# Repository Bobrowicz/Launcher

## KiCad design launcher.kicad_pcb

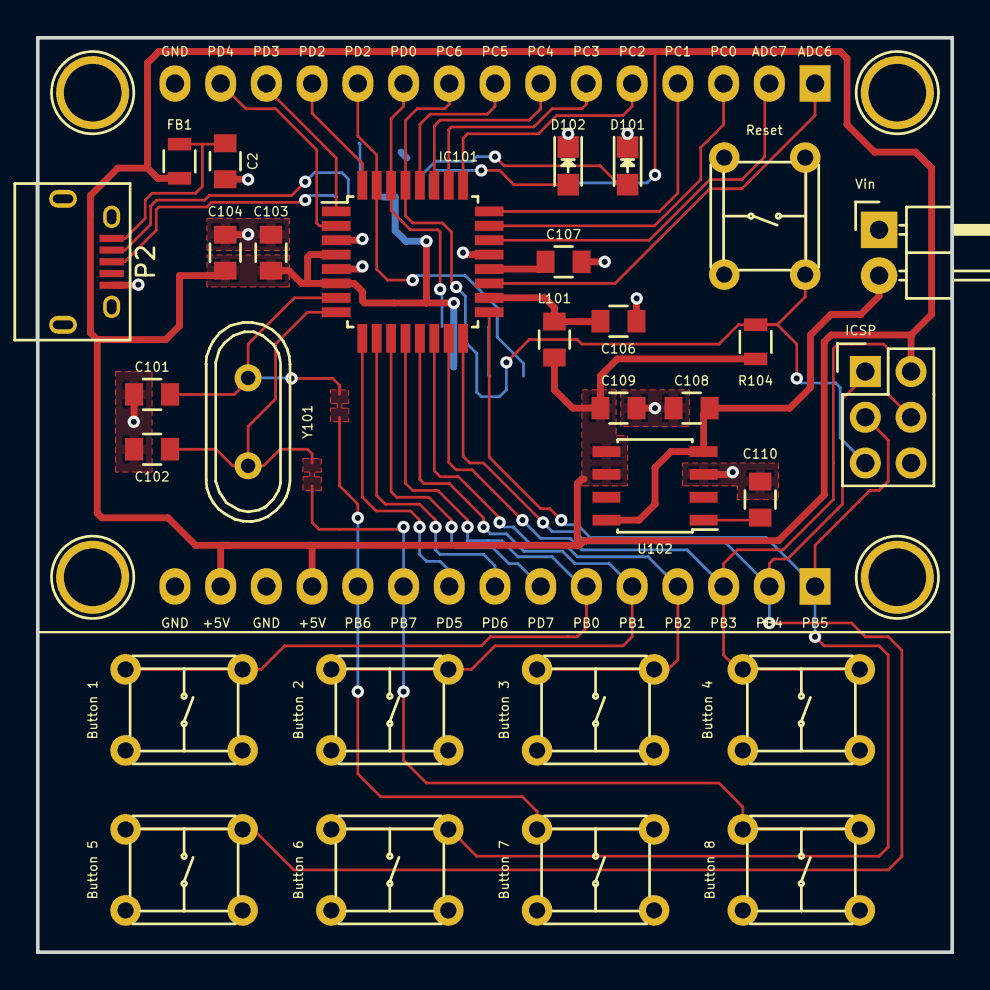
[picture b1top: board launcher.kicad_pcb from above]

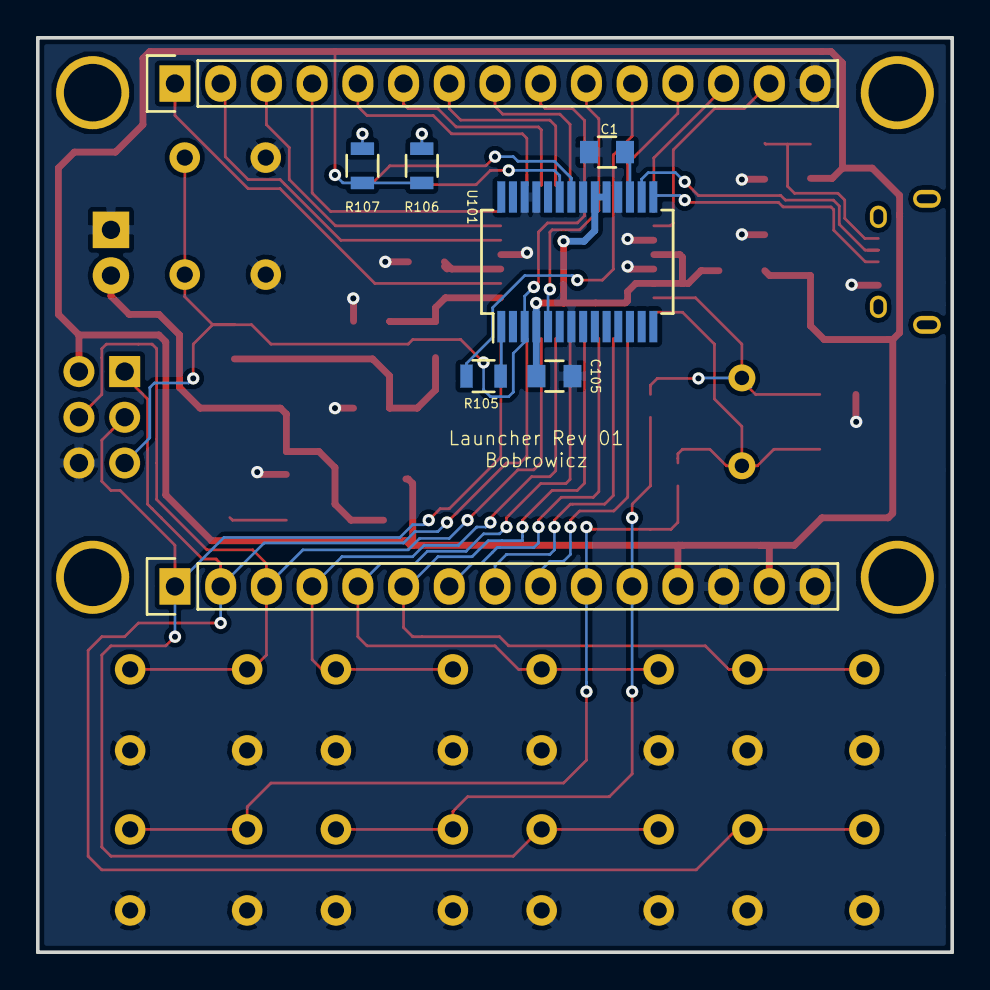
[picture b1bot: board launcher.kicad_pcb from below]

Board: 2 copper layers, 50.8 x 50.8 mm, 38 parts (8 on the bottom side), 40 nets.

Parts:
C1, C103, C106, C107: 100 nF; C_0805
C2, C104, C110: 10 nF; C_0805
C101, C102: 22 pF; C_0805
C105, C108: 4.7 uF; C_0805
C109: 10 uF; C_0805
D101: Green; LED-0805
D102: Red; LED-0805
FB1: 0R; R_0805
IC101: ATMEGA328-A; TQFP-32_7x7mm_Pitch0.8mm
ICSP: CONN_02X03; Pin_Header_Straight_2x03
L101: 10 uH; C_0805
P2: USB_OTG; USB_Micro-B
P102, P103: CONN_01X15; Pin_Header_Straight_1x15
R104: 4.7k; R_0805
R105: 10; R_0805
R106, R107: 240R; R_0805
SW101: Button 1; B3F-10XX
SW102: Button 2; B3F-10XX
SW103: Button 3; B3F-10XX
SW104: Button 4; B3F-10XX
SW105: Button 5; B3F-10XX
SW106: Button 6; B3F-10XX
SW107: Button 7; B3F-10XX
SW108: Button 8; B3F-10XX
SW109: Reset; B3F-10XX
U101: FT232RL; SSOP-28_5.3x10.2mm_Pitch0.65mm
U102: LP2989; SOIC-8_3.9x4.9mm_Pitch1.27mm
Vin: CONN_01X02; Pin_Header_Angled_1x02
Y101: Crystal; Crystal_HC49-U_Vertical

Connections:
+5V: C103.1, C104.1, C105.1, C109.1, FB1.1, IC101.4, IC101.6, ICSP.2, L101.1, P103.12, P103.14, R104.1, R106.1, R107.1, U101.4, U101.19, U101.20, U102.5, U102.6
/ADC6: IC101.19, P102.1
/ADC7: IC101.22, P102.2
/B0: IC101.12, P103.6, SW101.1, SW101.3
/B1: IC101.13, P103.5, SW102.1, SW102.3
/B2: IC101.14, P103.4, SW103.1, SW103.3
/B3: IC101.15, ICSP.4, P103.3, SW104.1, SW104.3
/B4: IC101.16, ICSP.1, P103.2, SW105.1, SW105.3
/B5: IC101.17, ICSP.3, P103.1, SW106.1, SW106.3
/B6: C101.1, IC101.7, P103.11, SW107.1, SW107.3, Y101.1
/B7: C102.1, IC101.8, P103.10, SW108.1, SW108.3, Y101.2
/PC0: IC101.23, P102.3
/PC1: IC101.24, P102.4
/PC2: IC101.25, P102.5
/PC3: IC101.26, P102.6
/PC4: IC101.27, P102.7
/PC5: IC101.28, P102.8
/PC6: IC101.29, ICSP.5, P102.9, R104.2, SW109.1, SW109.3, U101.3
/PD0: IC101.30, P102.10, U101.5
/PD1: IC101.31, P102.11, R105.1
/PD2: IC101.32, P102.12
/PD3: IC101.1, P102.13
/PD4: IC101.2, P102.14
/PD5: IC101.9, P103.9
/PD6: IC101.10, P103.8
/PD7: IC101.11, P103.7
/Vin: C108.1, U102.4, U102.8, Vin.2
GND: C1.2, C2.2, C101.2, C102.2, C103.2, C104.2, C105.2, C106.2, C107.2, C108.2, C109.2, C110.2, IC101.3, IC101.5, IC101.21, ICSP.6, P2.5, P102.15, P103.13, P103.15, SW101.2, SW101.4, SW102.2, SW102.4, SW103.2, SW103.4, SW104.2, SW104.4, SW105.2, SW105.4, SW106.2, SW106.4, SW107.2, SW107.4, SW108.2, SW108.4, SW109.2, SW109.4, U101.7, U101.18, U101.21, U101.25, U101.26, U102.3, Vin.1
unnamed: C1.1, U101.17
unnamed: C2.1, FB1.2, P2.1
unnamed: C106.1, IC101.18, L101.2
unnamed: C107.1, IC101.20
unnamed: C110.1, U102.1
unnamed: D101.1, R107.2
unnamed: D101.2, U101.22
unnamed: D102.1, R106.2
unnamed: D102.2, U101.23
unnamed: P2.2, U101.16
unnamed: P2.3, U101.15
unnamed: R105.2, U101.1

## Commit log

2016-05-08 :neckbeard: Added .gitattributes & .gitignore files
2016-05-08 Created repository
2016-05-11 added python script
    Python script runs on the PC and listens to serial port for data from
    microcontroller
2016-05-12 script tweak
    took out bunch of if statements and created a function instead
